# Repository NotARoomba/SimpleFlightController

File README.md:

<h1 align="center">
  <br>
  
  <br>
  Simple Flight Controller
  <br>
</h1>

<h4 align="center">
A comprehensive guide on building a flight controller from scratch for rockets!
</h4>

<div align="center">

</div>

<p align="center">
  <a href="#key-features">Key Features</a> •
  <a href="#guide">Guide</a> •
  <a href="#pcb">PCB</a> •
  <a href="#credits">Credits</a> •
  <a href="#license">License</a>
</p>

## Key Features

- **STM32F722RET6 microcontroller** for high-performance control
- **ICM-45686 IMU** for precise motion tracking
- **BMP580 barometer** for altitude sensing
- **MicroSD card storage** for flight data logging
- **Dual servo outputs** for TVC or fin control
- **2-cell LiPo support** with integrated BQ25883 charger
- **USB-C connectivity** for programming and data transfer
- **Compact design** optimized for rocket applications

## Guide

Check out the comprehensive [GUIDE.md](GUIDE.md) that walks you through:

- Component selection and requirements
- Schematic design with detailed explanations
- Communication protocols (I2C, SPI, UART, USB)
- PCB layout and routing best practices
- Power management circuitry
- Manufacturing with JLCPCB

## PCB

Designed in KiCad with careful attention to signal integrity, power distribution, and compact layout suitable for rocket applications.

### Schematic

### PCB Layout

## Credits

This project uses:

- [KiCad](https://www.kicad.org/)
- [STM32CubeMX](https://www.st.com/en/development-tools/stm32cubemx.html)
- [easyeda2kicad.py](https://github.com/uPesy/easyeda2kicad.py)
- [Hack Club Blueprint](https://blueprint.hackclub.com/)

## You may also like...

- [Trace](https://github.com/NotARoomba/Trace) – A comprehensive PCB ruler with reference footprints
- [Cyberboard](https://github.com/NotARoomba/Cyberboard) – A Raspberry Pi Pico-sized STM32 development board with Bluetooth
- [CyberCard](https://github.com/NotARoomba/CyberCard) – A Cyberpunk themed NFC hacker card
- [Niveles De Niveles](https://github.com/NotARoomba/NivelesDeNiveles) – Real-time flood alert app
- [Linea](https://github.com/NotARoomba/Linea) – An EMR tablet
- [Tamaki](https://github.com/NotARoomba/Tamaki) – A cute HackPad

## License

MIT

---

> [notaroomba.dev](https://notaroomba.dev) &nbsp;&middot;&nbsp;
> GitHub [@NotARoomba](https://github.com/NotARoomba) &nbsp;&middot;&nbsp;

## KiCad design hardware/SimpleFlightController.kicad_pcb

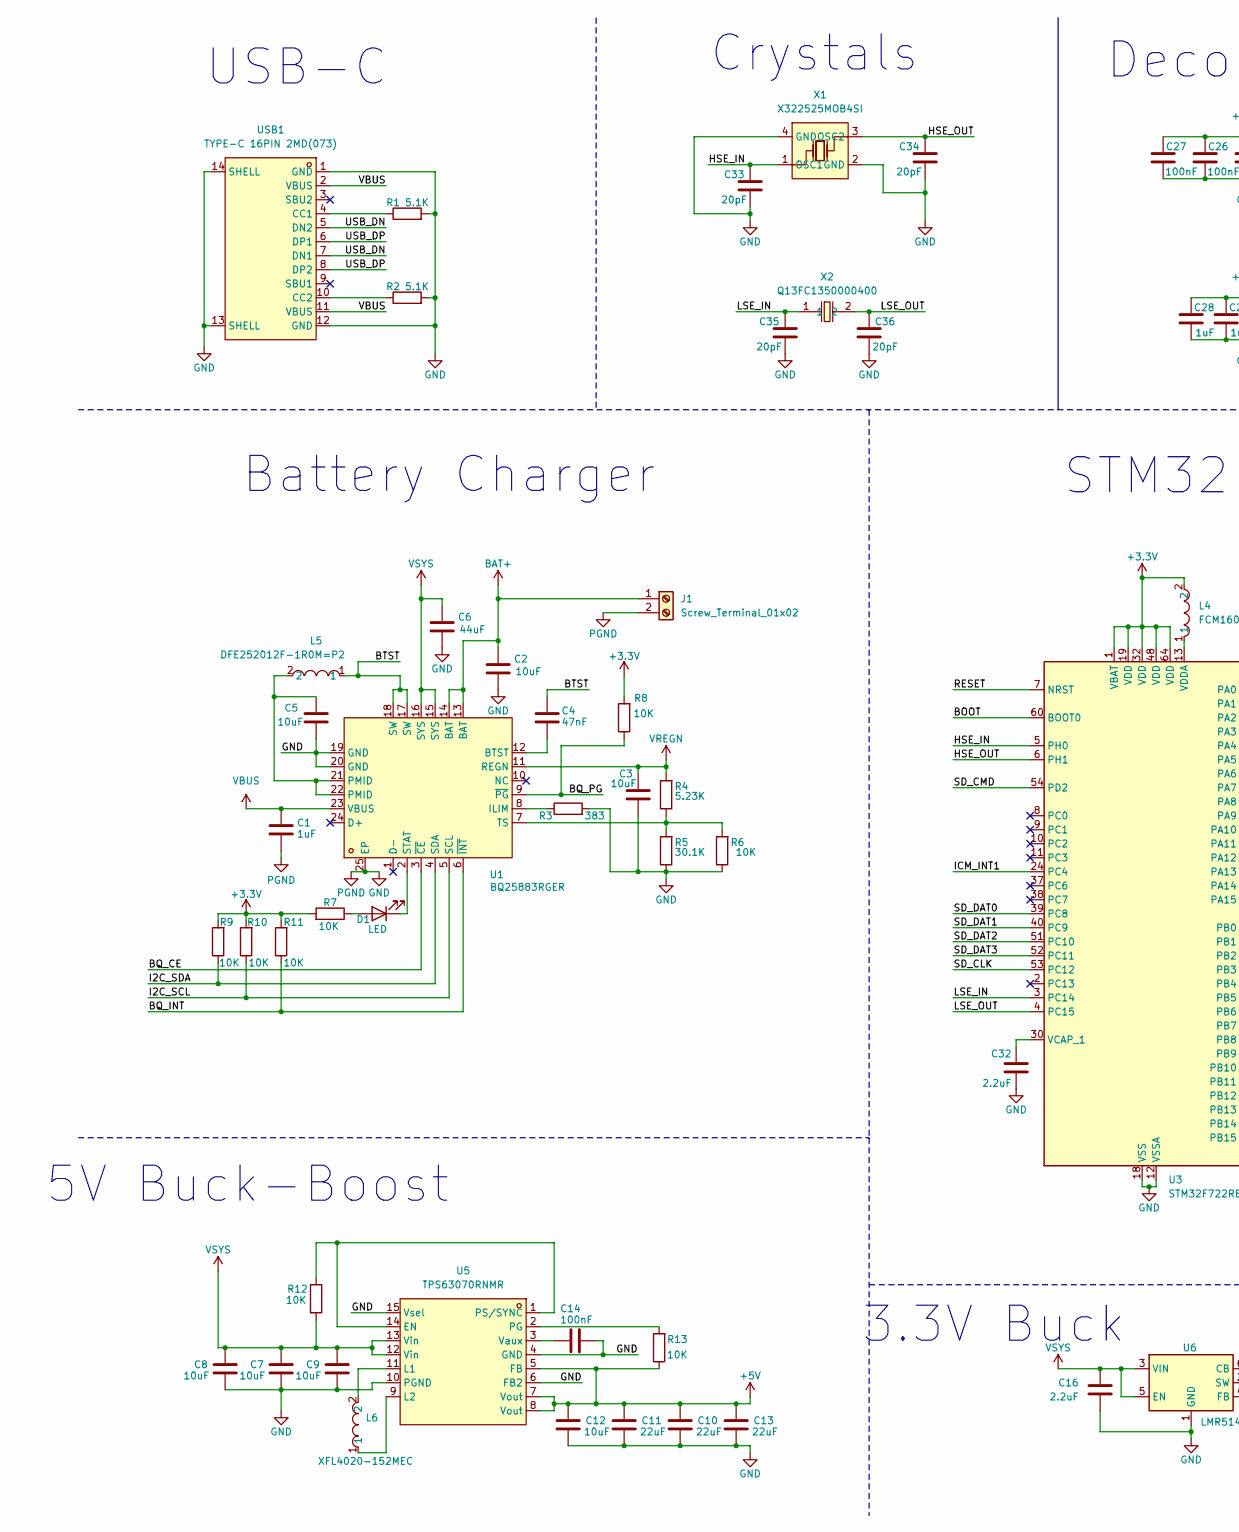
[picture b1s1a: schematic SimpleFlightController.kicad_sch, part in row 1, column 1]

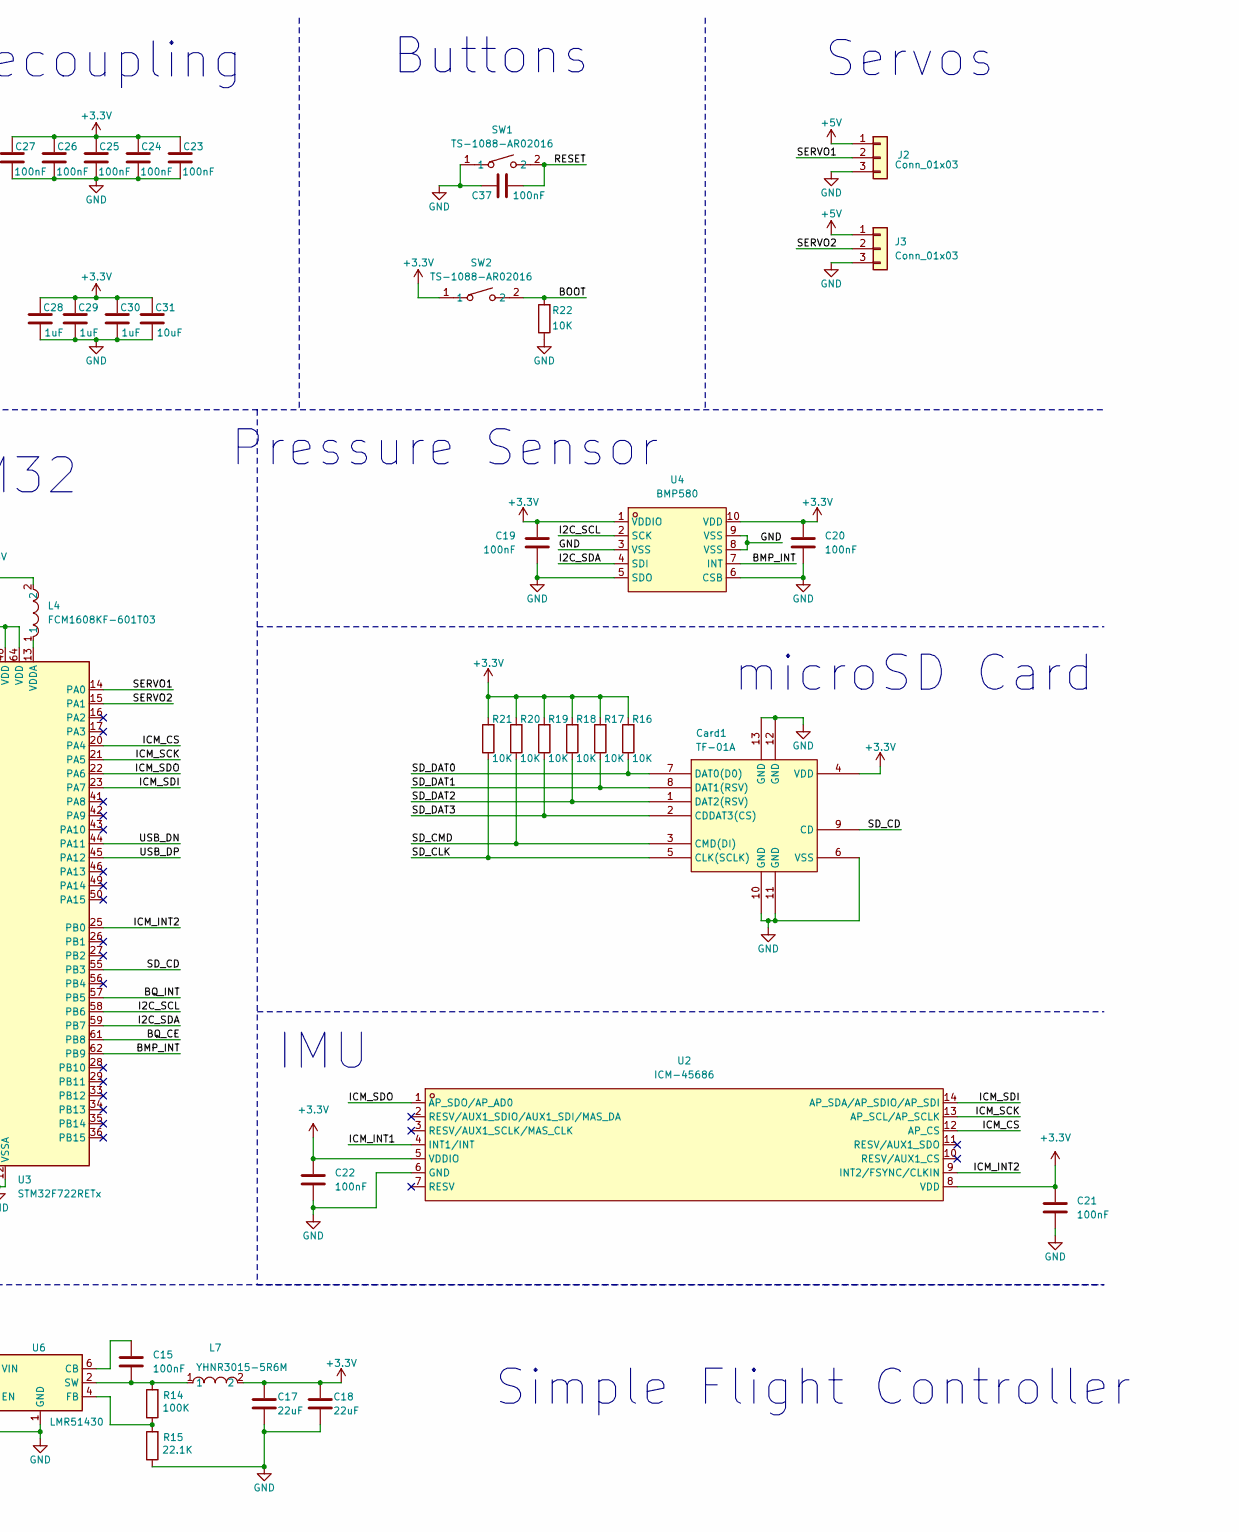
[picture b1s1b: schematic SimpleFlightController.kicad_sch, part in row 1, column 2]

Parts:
C1, C28, C29, C30: 1uF; C_0402_1005Metric
C2, C9, C12: 10uF; C_0603_1608Metric
C3, C5, C31: 10uF; C_0402_1005Metric
C4: 47nF; C_0201_0603Metric
C6: 44uF; C_0603_1608Metric
C7, C8: 10uF; C_0805_2012Metric
C10, C11, C13: 22uF; C_0805_2012Metric
C14, C15, C19, C20, C21, C22, C23, C24, C25, C26, C27, C37: 100nF; C_0201_0603Metric
C16: 2.2uF; C_0603_1608Metric
C17, C18: 22uF; C_0402_1005Metric
C32: 2.2uF; C_0201_0603Metric
C33, C34, C35, C36: 20pF; C_0201_0603Metric
Card1: TF-01A; TF-SMD_TF-01A; LCSC Part C91145
D1: LED; LED_0402_1005Metric
J1: Screw_Terminal_01x02; TerminalBlock_Xinya_XY308-2.54-2P_1x02_P2.54mm_Horizontal
J2, J3: Conn_01x03; PinHeader_1x03_P2.54mm_Vertical
L4: FCM1608KF-601T03; L0603; LCSC Part C141723
L5: DFE252012F-1R0M=P2; L2520; LCSC Part C435392
L6: XFL4020-152MEC; IND-SMD_L4.0-W4.0-A; LCSC Part C3033018
L7: YHNR3015-5R6M; IND-SMD_L3.0-W3.0; LCSC Part C18236327
R1, R2: 5.1K; R_0201_0603Metric
R3: 383; R_0201_0603Metric
R4: 5.23K; R_0201_0603Metric
R5: 30.1K; R_0201_0603Metric
R6, R7, R8, R9, R10, R11, R12, R13, R16, R17, R18, R19, R20, R21, R22: 10K; R_0201_0603Metric
R14: 100K; R_0402_1005Metric
R15: 22.1K; R_0402_1005Metric
SW1, SW2: TS-1088-AR02016; SW-SMD_L3.9-W3.0-P4.45; LCSC Part C720477
U1: BQ25883RGER; VFQFPN-24_L4.0-W4.0-P0.50-BL-EP2.8; LCSC Part C544362
U2: ICM-45686; LGA-14_L3.0-W2.5-P0.50-TL; LCSC Part C22459454
U3: STM32F722RETx; LQFP-64_10x10mm_P0.5mm
U4: BMP580; LGA-10_L2.0-W2.0-P0.50-TL_BMP580; LCSC Part C22391138
U5: TPS63070RNMR; VQFN-HR-15_L3.0-W2.5-P0.50-BL_TPS63070RNMR; LCSC Part C109322
U6: LMR51430; SOT-23-6
USB1: TYPE-C 16PIN 2MD(073); USB-C-SMD_TYPE-C-6PIN-2MD-073; LCSC Part C2765186
X1: X322525MOB4SI; CRYSTAL-SMD_4P-L3.2-W2.5-BL; LCSC Part C9006
X2: Q13FC1350000400; FC-135R_L3.2-W1.5; LCSC Part C32346

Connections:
+3.3V: C17.1, C18.1, C19.1, C20.1, C21.1, C22.1, C23.1, C24.1, C25.1, C26.1, C27.1, C28.1, C29.1, C30.1, C31.1, Card1.4 (VDD), L4.2, L7.2, R7.2, R8.2, R9.2, R10.2, R11.2, R16.2, R17.2, R18.2, R19.2, R20.2, R21.2, SW2.1, U2.5 (VDDIO), U2.8 (VDD), U3.1 (VBAT), U3.19 (VDD), U3.32 (VDD), U3.48 (VDD), U3.64 (VDD), U4.1 (VDDIO), U4.10 (VDD)
+5V: C10.1, C11.1, C12.1, C13.1, J2.1, J3.1, R13.1, U5.5 (FB), U5.7 (Vout), U5.8 (Vout)
/BMP_INT: U3.62 (PB9), U4.7 (INT)
/BOOT: R22.2, SW2.2, U3.60 (BOOT0)
/BQ_CE: U1.3 (~CE), U3.61 (PB8)
/BQ_INT: R11.1, U1.6 (~INT), U3.57 (PB5)
/BQ_PG: R8.1, U1.9 (~PG)
/BTST: C4.1, L5.1, U1.17 (SW), U1.18 (SW)
/HSE_IN: C33.1, U3.5 (PH0), X1.1 (OSC1)
/HSE_OUT: C34.1, U3.6 (PH1), X1.3 (OSC2)
/I2C_SCL: R10.1, U1.5 (SCL), U3.58 (PB6), U4.2 (SCK)
/I2C_SDA: R9.1, U1.4 (SDA), U3.59 (PB7), U4.4 (SDI)
/ICM_CS: U2.12 (AP_CS), U3.20 (PA4)
/ICM_INT1: U2.4 (INT1/INT), U3.24 (PC4)
/ICM_INT2: U2.9 (INT2/FSYNC/CLKIN), U3.25 (PB0)
/ICM_SCK: U2.13 (AP_SCL/AP_SCLK), U3.21 (PA5)
/ICM_SDI: U2.14 (AP_SDA/AP_SDIO/AP_SDI), U3.23 (PA7)
/ICM_SDO: U2.1 (AP_SDO/AP_AD0), U3.22 (PA6)
/LSE_IN: C35.1, U3.3 (PC14), X2.1
/LSE_OUT: C36.1, U3.4 (PC15), X2.2
/RESET: C37.2, SW1.2, U3.7 (NRST)
/SD_CD: Card1.9 (CD), U3.55 (PB3)
/SD_CLK: Card1.5 (CLK(SCLK)), R21.1, U3.53 (PC12)
/SD_CMD: Card1.3 (CMD(DI)), R20.1, U3.54 (PD2)
/SD_DAT0: Card1.7 (DAT0(D0)), R16.1, U3.39 (PC8)
/SD_DAT1: Card1.8 (DAT1(RSV)), R17.1, U3.40 (PC9)
/SD_DAT2: Card1.1 (DAT2(RSV)), R18.1, U3.51 (PC10)
/SD_DAT3: Card1.2 (CDDAT3(CS)), R19.1, U3.52 (PC11)
/SERVO1: J2.2, U3.14 (PA0)
/SERVO2: J3.2, U3.15 (PA1)
/USB_DN: U3.44 (PA11), USB1.5 (DN2), USB1.7 (DN1)
/USB_DP: U3.45 (PA12), USB1.6 (DP1), USB1.8 (DP2)
BAT+: C2.1, J1.1, U1.13 (BAT), U1.14 (BAT)
GND: C1.2, C2.2, C3.2, C5.2, C6.2, C7.2, C8.2, C9.2, C10.2, C11.2, C12.2, C13.2, C14.2, C16.2, C17.2, C18.2, C19.2, C20.2, C21.2, C22.2, C23.2, C24.2, C25.2, C26.2, C27.2, C28.2, C29.2, C30.2, C31.2, C32.2, C33.2, C34.2, C35.2, C36.2, C37.1, Card1.6 (VSS), Card1.10 (GND), Card1.11 (GND), Card1.12 (GND), Card1.13 (GND), J1.2, J2.3, J3.3, R1.2, R2.2, R3.2, R5.1, R6.1, R15.1, R22.1, SW1.1, U1.19 (GND), U1.20 (GND), U1.25 (EP), U2.6 (GND), U3.12 (VSSA), U3.18 (VSS), U3.31 (VSS), U3.47 (VSS), U3.63 (VSS), U4.3 (VSS), U4.5 (SDO), U4.6 (CSB), U4.8 (VSS), U4.9 (VSS), U5.4 (GND), U5.6 (FB2), U5.10 (PGND), U5.15 (Vsel), U6.1 (GND), USB1.1 (GND), USB1.12 (GND), USB1.13 (SHELL), USB1.14 (SHELL), X1.2 (GND), X1.4 (GND)
unnamed: C5.1, L5.2, U1.21 (PMID), U1.22 (PMID)
unnamed: D1.2 (A), R7.1
unnamed: D1.1 (K), U1.2 (STAT)
unnamed: C4.2, U1.12 (BTST)
unnamed: R3.1, U1.8 (ILIM)
unnamed: R4.1, R5.2, R6.2, U1.7 (TS)
unnamed: C32.1, U3.30 (VCAP_1)
unnamed: L4.1, U3.13 (VDDA)
unnamed: R12.1, U5.1 (PS/SYNC), U5.14 (EN)
unnamed: L6.2, U5.11 (L1)
unnamed: L6.1, U5.9 (L2)
unnamed: R13.2, U5.2 (PG)
unnamed: C14.1, U5.3 (Vaux)
unnamed: C15.1, U6.6 (CB)
unnamed: R14.1, R15.2, U6.4 (FB)
unnamed: C15.2, L7.1, R14.2, U6.2 (SW)
unnamed: R1.1, USB1.4 (CC1)
unnamed: R2.1, USB1.10 (CC2)
VBUS: C1.1, U1.23 (VBUS), USB1.2 (VBUS), USB1.11 (VBUS)
VREGN: C3.1, R4.2, U1.11 (REGN)
VSYS: C6.1, C7.1, C8.1, C9.1, C16.1, R12.2, U1.15 (SYS), U1.16 (SYS), U5.12 (Vin), U5.13 (Vin), U6.3 (VIN), U6.5 (EN)

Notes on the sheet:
Simple Flight Controller
Pressure Sensor
Decoupling
3.3V Buck
Buttons
IMU
USB-C
Servos
Battery Charger
STM32
Crystals
microSD Card
5V Buck-Boost

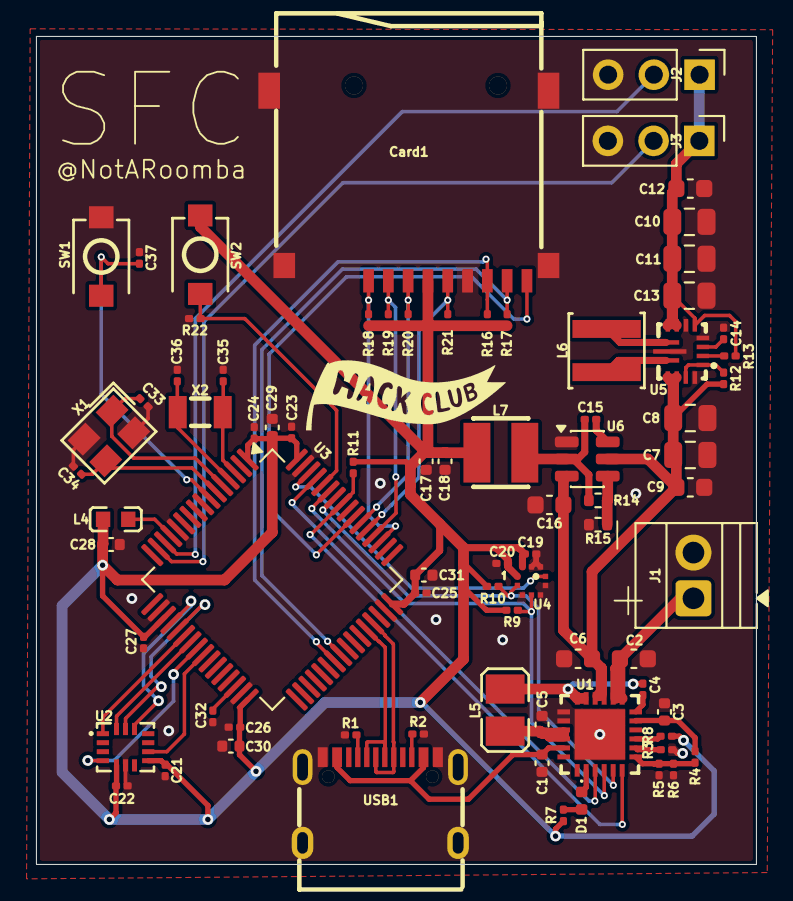
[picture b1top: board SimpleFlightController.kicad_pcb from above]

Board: 2 copper layers, 40.0 x 46.0 mm, 79 parts (0 on the bottom side), 55 nets.

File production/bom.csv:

Designator,Footprint,Quantity,Value,LCSC Part #
"BOOT, RESET",SW-SMD_L3.9-W3.0-P4.45,2,TS-1088-AR02016,C720477
"C1, C28, C29, C30",0402,4,1uF,
"C10, C11, C13",0805,3,22uF,
"C12, C2, C9",0603,3,10uF,
"C14, C15, C19, C20, C21, C22, C23, C24, C25, C26, C27, C37",0201,12,100nF,
C16,0603,1,2.2uF,
"C17, C18",0402,2,22uF,
"C3, C31, C5",0402,3,10uF,
C32,0201,1,2.2uF,
"C33, C34, C35, C36",0201,4,20pF,
C4,0201,1,47nF,
C6,0603,1,44uF,
"C7, C8",0805,2,10uF,
CARD1,TF-SMD_TF-01A,1,TF-01A,C91145
D1,0402,1,LED,
J1,TerminalBlock_Xinya_XY308-2.54-2P_1x02_P2.54mm_Horizontal,1,Screw_Terminal_01x02,
"J2, J3",PinHeader_1x03_P2.54mm_Vertical,2,Conn_01x03,
L4,L0603,1,FCM1608KF-601T03,C141723
L5,L2520,1,DFE252012F-1R0M=P2,C435392
L6,IND-SMD_L4.0-W4.0-A,1,XFL4020-152MEC,C3033018
L7,IND-SMD_L3.0-W3.0,1,YHNR3015-5R6M,C18236327
"R1, R2",0201,2,5.1K,
"R10, R11, R12, R13, R16, R17, R18, R19, R20, R21, R22, R6, R7, R8, R9",0201,15,10K,
R14,0402,1,100K,
R15,0402,1,22.1K,
R3,0201,1,383,
R4,0201,1,5.23K,
R5,0201,1,30.1K,
U1,VFQFPN-24_L4.0-W4.0-P0.50-BL-EP2.8,1,BQ25883RGER,C544362
U2,LGA-14_L3.0-W2.5-P0.50-TL,1,ICM-45686,C22459454
U3,LQFP-64_10x10mm_P0.5mm,1,STM32F722RETx,
U4,LGA-10_L2.0-W2.0-P0.50-TL_BMP580,1,BMP580,C22391138
U5,VQFN-HR-15_L3.0-W2.5-P0.50-BL_TPS63070RNMR,1,TPS63070RNMR,C109322
U6,SOT-23-6,1,LMR51430,
USB1,USB-C-SMD_TYPE-C-6PIN-2MD-073,1,TYPE-C 16PIN 2MD(073),C2765186
X1,CRYSTAL-SMD_4P-L3.2-W2.5-BL,1,X322525MOB4SI,C9006
X2,FC-135R_L3.2-W1.5,1,Q13FC1350000400,C32346

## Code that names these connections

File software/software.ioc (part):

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Mcu.Name=STM32F722R(C-E)Tx
Mcu.Package=LQFP64
Mcu.UserName=STM32F722RETx
PA0-WKUP.Signal=S_TIM2_CH1_ETR
PA1.Signal=S_TIM2_CH2
PA11.Mode=Host_Only
PA11.Signal=USB_OTG_FS_DM
PA12.Mode=Host_Only
PA12.Signal=USB_OTG_FS_DP
PA4.Mode=NSS_Signal_Hard_Output
PA4.Signal=SPI1_NSS
PA5.Mode=Full_Duplex_Master
PA5.Signal=SPI1_SCK
PA6.Mode=Full_Duplex_Master
PA6.Signal=SPI1_MISO
PA7.Mode=Full_Duplex_Master
PA7.Signal=SPI1_MOSI
PB0.GPIOParameters=GPIO_Label
PB0.GPIO_Label=ICM_INT2
PB0.Signal=GPXTI0
PB3.GPIOParameters=GPIO_Label
PB3.GPIO_Label=SD_CS
PB3.Signal=GPIO_Input
PB5.GPIOParameters=GPIO_Label
PB5.GPIO_Label=BQ_INT
PB5.Signal=GPXTI5
PB6.Mode=I2C
PB6.Signal=I2C1_SCL
PB7.Mode=I2C
PB7.Signal=I2C1_SDA
PB8.GPIOParameters=GPIO_Label
PB8.GPIO_Label=BQ_CE
PB8.Signal=GPIO_Output
PB9.GPIOParameters=GPIO_Label
PB9.GPIO_Label=BMP_INT
PB9.Signal=GPXTI9
PC10.Mode=SD_4_bits_Wide_bus
PC10.Signal=SDMMC1_D2
PC11.Mode=SD_4_bits_Wide_bus
PC11.Signal=SDMMC1_D3
PC12.Mode=SD_4_bits_Wide_bus
PC12.Signal=SDMMC1_CK
PC14-OSC32_IN.Mode=LSE-External-Oscillator
PC14-OSC32_IN.Signal=RCC_OSC32_IN
PC15-OSC32_OUT.Mode=LSE-External-Oscillator
PC15-OSC32_OUT.Signal=RCC_OSC32_OUT
PC4.GPIOParameters=GPIO_Label
PC4.GPIO_Label=ICM_INT1
PC4.Signal=GPXTI4
PC8.Mode=SD_4_bits_Wide_bus
PC8.Signal=SDMMC1_D0
PC9.Mode=SD_4_bits_Wide_bus
PC9.Signal=SDMMC1_D1
PD2.Mode=SD_4_bits_Wide_bus
PD2.Signal=SDMMC1_CMD
PH0-OSC_IN.Mode=HSE-External-Oscillator
PH0-OSC_IN.Signal=RCC_OSC_IN
PH1-OSC_OUT.Mode=HSE-External-Oscillator
PH1-OSC_OUT.Signal=RCC_OSC_OUT
RCC.HSE_VALUE=25000000
RCC.SYSCLKFreq_VALUE=40000000
RCC.SYSCLKSource=RCC_SYSCLKSOURCE_PLLCLK
board=custom

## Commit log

2025-10-26 add kicad stard and omponents
2025-10-26 stuff
2025-10-27 finished the 5v buck boost section
2025-10-27 images
2025-10-27 added more stuff
2025-11-02 schematic done
2025-11-03 added stuff
2025-11-06 finish guide and board
2025-11-06 grammar check and images
2025-11-06 add readme and bom
2025-11-06 bo mand cart
2025-11-07 add stm32 programmign guide
2025-11-11 updated firmware section
2025-11-11 update image paths and 3d render
2025-11-11 start blender render and hc flag
2025-11-11 fix missing images
2025-11-11 fix readme
2025-11-11 guide and render webp
2025-11-22 flip led
2025-11-22 guide
2025-11-28 Create update-guide.code-workspace
2026-01-12 fixstuff
2026-05-19 aaaaaa
